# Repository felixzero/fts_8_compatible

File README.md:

# FTS-8 compatible board

Redesign of a replacement for the FTS-8 board for Yaesu transceivers.

Technical details: https://guilloy.fr/?p=655

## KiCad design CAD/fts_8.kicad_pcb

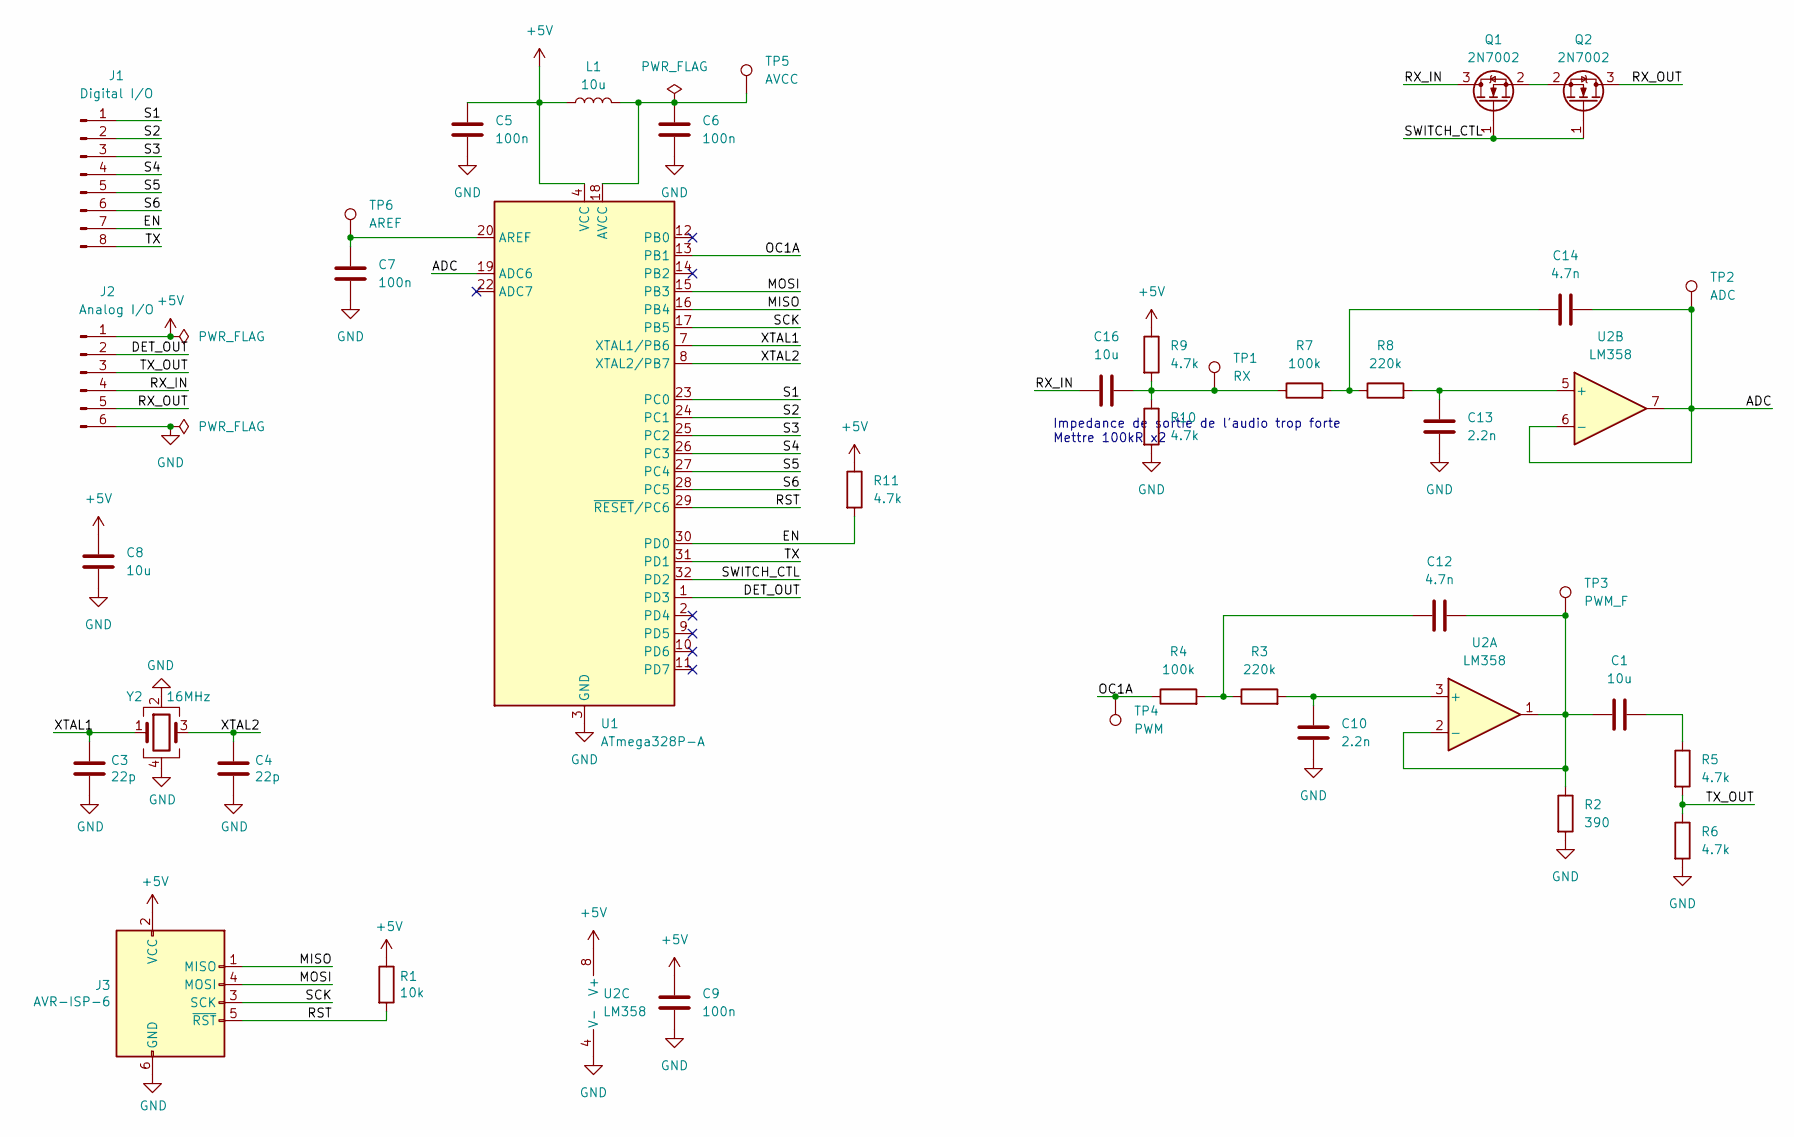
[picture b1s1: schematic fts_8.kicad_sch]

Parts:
C1, C8, C16: 10u; C_0603_1608Metric
C3, C4: 22p; C_0603_1608Metric
C5, C6, C7, C9: 100n; C_0603_1608Metric
C10, C13: 2.2n; C_0805_2012Metric
C12, C14: 4.7n; C_0603_1608Metric
J1: Digital I/O; PinHeader_1x08_P2.54mm_Vertical
J2: Analog I/O; PinHeader_1x06_P2.54mm_Vertical
J3: AVR-ISP-6; PinHeader_2x03_P2.54mm_Vertical
L1: 10u; L_0805_2012Metric
Q1, Q2: 2N7002; SOT-23
R1: 10k; R_0603_1608Metric
R2: 390; R_0603_1608Metric
R3, R8: 220k; R_0603_1608Metric
R4, R7: 100k; R_0603_1608Metric
R5, R6, R9, R10, R11: 4.7k; R_0603_1608Metric
TP1: RX; TestPoint_THTPad_D1.0mm_Drill0.5mm
TP2: ADC; TestPoint_THTPad_D1.0mm_Drill0.5mm
TP3: PWM_F; TestPoint_THTPad_D1.0mm_Drill0.5mm
TP4: PWM; TestPoint_THTPad_D1.0mm_Drill0.5mm
TP5: AVCC; TestPoint_THTPad_D1.0mm_Drill0.5mm
TP6: AREF; TestPoint_THTPad_D1.0mm_Drill0.5mm
U1: ATmega328P-A; TQFP-32_7x7mm_P0.8mm
U2: LM358; SOIC-8_3.9x4.9mm_P1.27mm
Y2: 16MHz; Crystal_SMD_TXC_7M-4Pin_3.2x2.5mm

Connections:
+5V: C5.1, C8.1, C9.1, J2.1, J3.2 (VCC), L1.1, R1.1, R9.1, R11.1, U1.4 (VCC), U1.6 (VCC), U2.8 (V+)
/ADC: C14.2, TP2.1, U1.19 (ADC6), U2.6 (-), U2.7
/DET_OUT: J2.2, U1.1 (PD3)
/EN: J1.7, R11.2, U1.30 (PD0)
/MISO: J3.1 (MISO), U1.16 (PB4)
/MOSI: J3.4 (MOSI), U1.15 (PB3)
/OC1A: R4.1, TP4.1, U1.13 (PB1)
/RST: J3.5 (~RST), R1.2, U1.29 (~RESET/PC6)
/RX_IN: C16.1, J2.4, Q1.3 (D)
/RX_OUT: J2.5, Q2.3 (D)
/S1: J1.1, U1.23 (PC0)
/S2: J1.2, U1.24 (PC1)
/S3: J1.3, U1.25 (PC2)
/S4: J1.4, U1.26 (PC3)
/S5: J1.5, U1.27 (PC4)
/S6: J1.6, U1.28 (PC5)
/SCK: J3.3 (SCK), U1.17 (PB5)
/SWITCH_CTL: Q1.1 (G), Q2.1 (G), U1.32 (PD2)
/TX: J1.8, U1.31 (PD1)
/TX_OUT: J2.3, R5.2, R6.1
/XTAL1: C3.1, U1.7 (XTAL1/PB6), Y2.1
/XTAL2: C4.1, U1.8 (XTAL2/PB7), Y2.3
GND: C3.2, C4.2, C5.2, C6.2, C7.2, C8.2, C9.2, C10.2, C13.2, J2.6, J3.6 (GND), R2.2, R6.2, R10.2, U1.3 (GND), U1.5 (GND), U1.21 (GND), U2.4 (V-), Y2.2, Y2.4
unnamed: C1.2, R5.1
unnamed: C12.1, R3.1, R4.2
unnamed: C14.1, R7.2, R8.1
unnamed: C16.2, R7.1, R9.2, R10.1, TP1.1
unnamed: Q1.2 (S), Q2.2 (S)
unnamed: C7.1, TP6.1, U1.20 (AREF)
unnamed: C6.1, L1.2, TP5.1, U1.18 (AVCC)
unnamed: C10.1, R3.2, U2.3 (+)
unnamed: C1.1, C12.2, R2.1, TP3.1, U2.1, U2.2 (-)
unnamed: C13.1, R8.2, U2.5 (+)

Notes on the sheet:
Impedance de sortie de l'audio trop forte Mettre 100kR x2

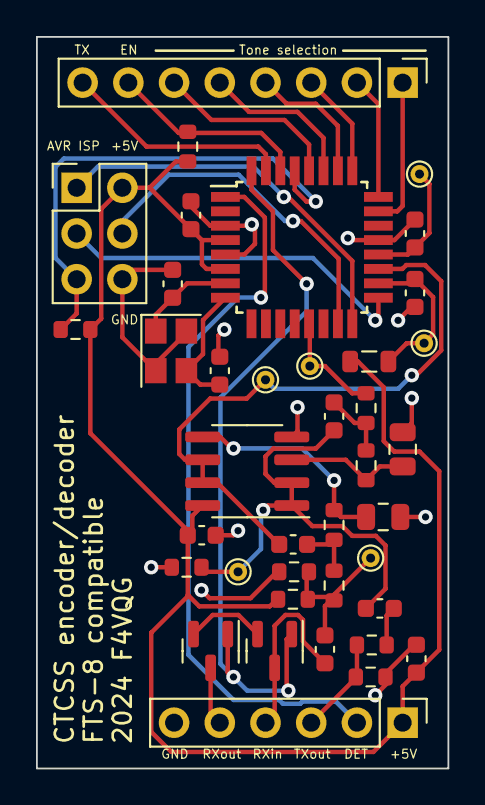
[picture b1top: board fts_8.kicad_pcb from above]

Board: 2 copper layers, 22.9 x 40.6 mm, 39 parts (0 on the bottom side), 33 nets.

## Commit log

2024-07-07 Initial version.
2024-11-11 Add missing non standard tones
